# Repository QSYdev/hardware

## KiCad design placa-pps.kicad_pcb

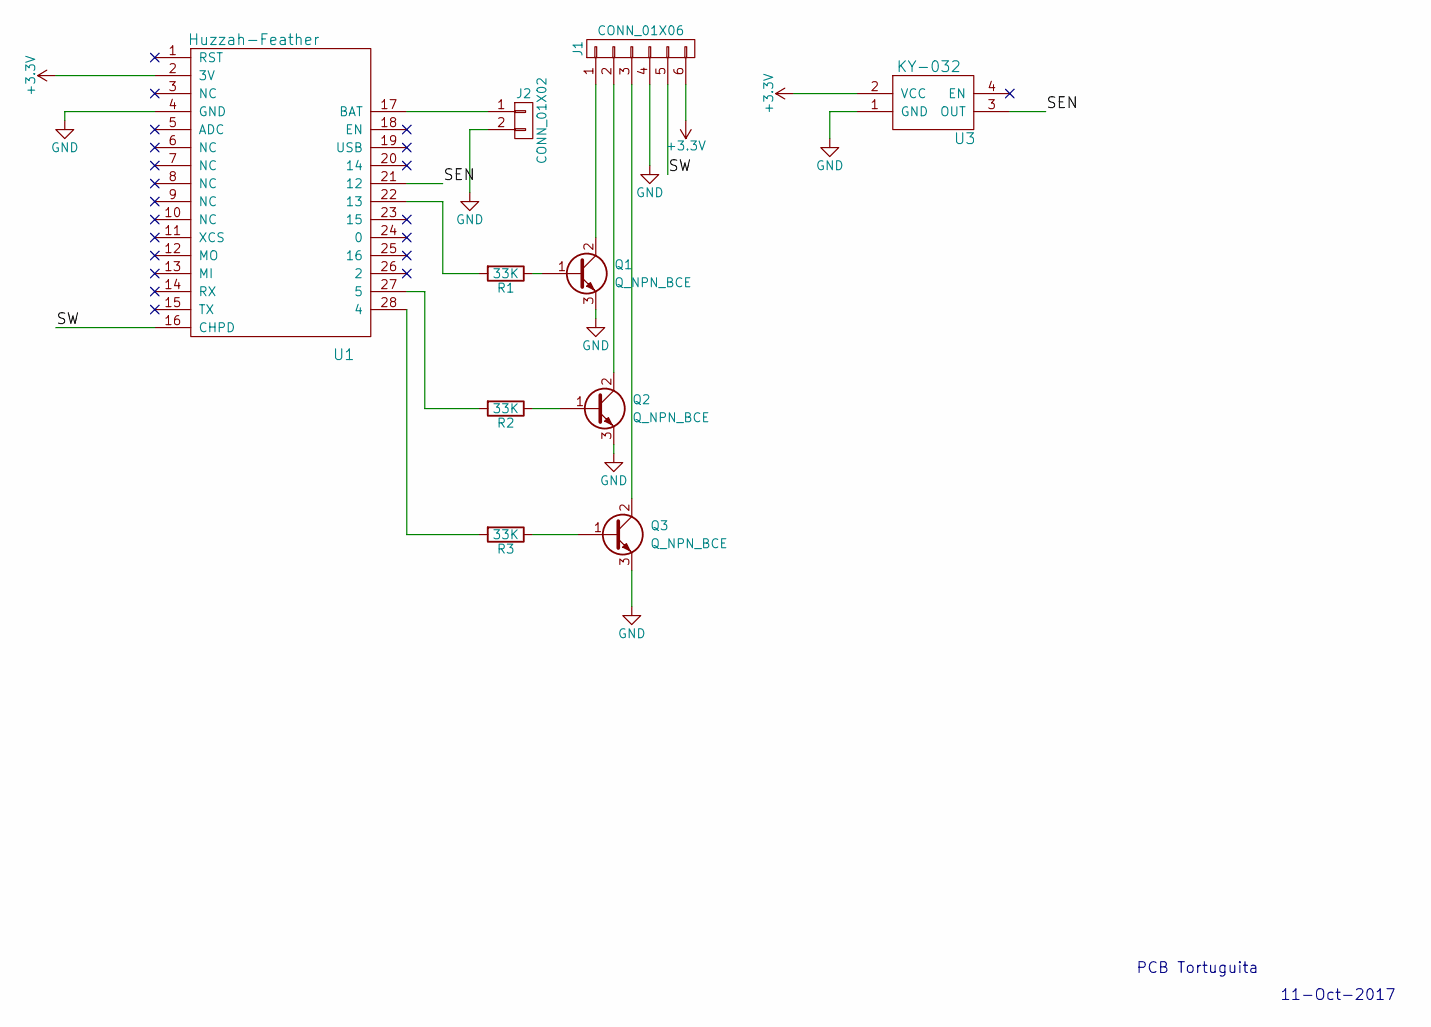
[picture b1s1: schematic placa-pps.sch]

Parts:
J1: CONN_01X06; Pin_Header_Straight_1x06_Pitch2.54mm
J2: CONN_01X02; Pin_Header_Straight_1x02_Pitch2.54mm
Q1, Q2, Q3: Q_NPN_BCE; TO-92_Inline_Narrow_Oval
R1, R2, R3: 33K; R_Axial_DIN0207_L6.3mm_D2.5mm_P7.62mm_Horizontal
U1: Huzzah-Feather; Huzzah_Feather_ESP8266
U3: KY-032

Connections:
+3V3: J1.6, U1.2 (3V), U3.2 (VCC)
/SEN: U1.21 (12), U3.3 (OUT)
/SW: J1.5, U1.16 (CHPD)
GND: J1.4, J2.2, Q1.3 (E), Q2.3 (E), Q3.3 (E), U1.4 (GND), U3.1 (GND)
unnamed: J1.1, Q1.2 (C)
unnamed: J1.2, Q2.2 (C)
unnamed: J1.3, Q3.2 (C)
unnamed: J2.1, U1.17 (BAT)
unnamed: Q1.1 (B), R1.1
unnamed: Q2.1 (B), R2.1
unnamed: Q3.1 (B), R3.1
unnamed: R1.2, U1.22 (13)
unnamed: R2.2, U1.27 (5)
unnamed: R3.2, U1.28 (4)

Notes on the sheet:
PCB Tortuguita
11-Oct-2017

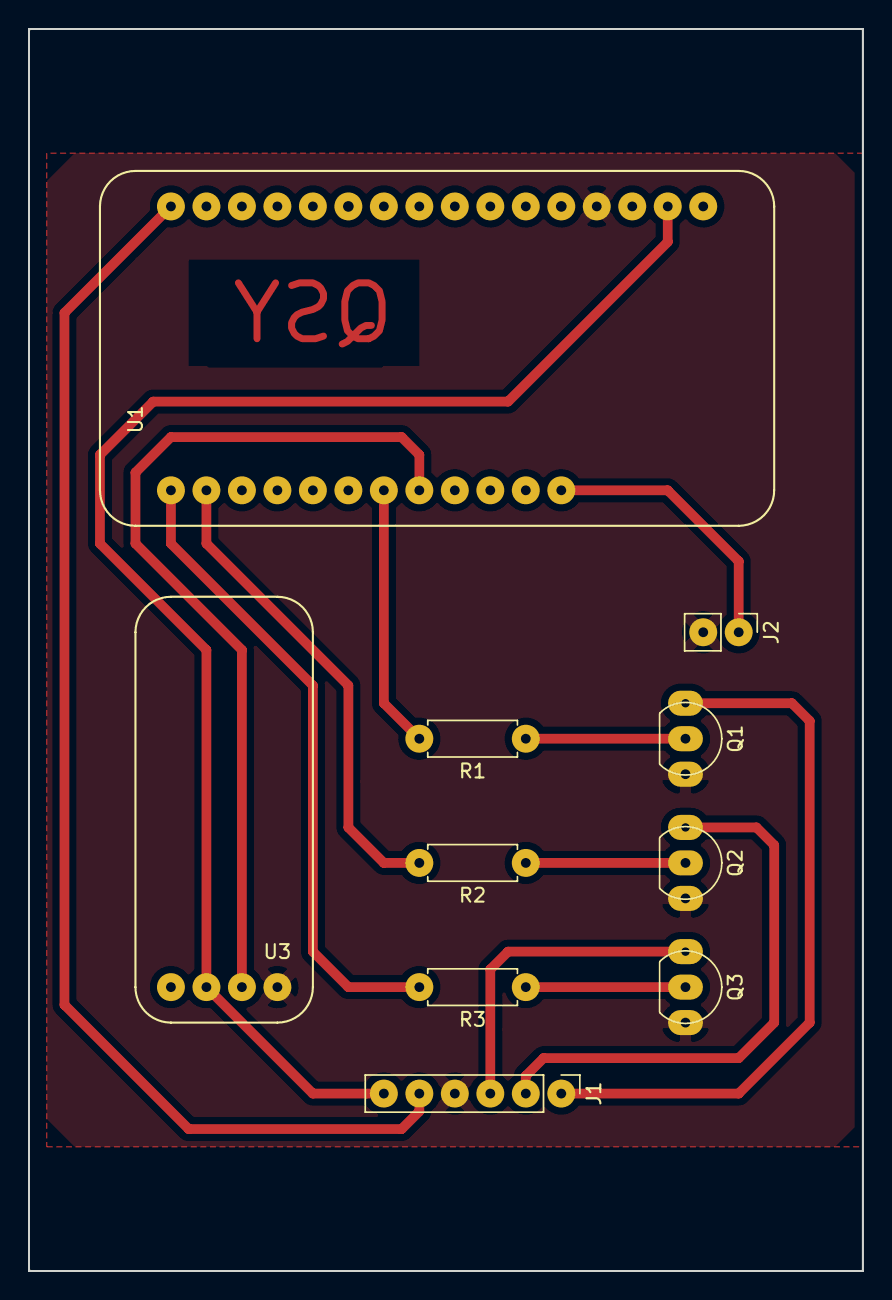
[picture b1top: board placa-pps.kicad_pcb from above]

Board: 2 copper layers, 59.7 x 88.9 mm, 10 parts (0 on the bottom side), 14 nets.

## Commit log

2017-10-12 Inicial
2017-10-12 Gitignore
2017-10-12 Correcciones
